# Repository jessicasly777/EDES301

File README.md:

Main control flow of this project 
Blynk App (Joystick)
        ↓
communication.py
        ↓
main.py (control logic)
        ↓
dc_motor.py
        ↓
DRV8833 → Motors

communication.py: Handles all communication between the PocketBeagle and the Blynk mobile application. It connects to the Blynk cloud and reads joystick input from two virtual pins:

V0 for left/right (X-axis)
V1 for forward/backward (Y-axis)

dc_motor.py: Cntrols the DC motors through the DRV8833 motor driver. Each motor is controlled using two pins:

A PWM pin for speed control
A GPIO pin for direction

The module provides simple methods:

forward(speed)
backward(speed)
stop()
cleanup()

limit_switch.py: This module implements an emergency stop mechanism using a physical limit switch.

pin.sh: Cnfigures the PocketBeagle pins before running the system.

main.py: Initializes all components, including the communication module, motor drivers, and limit switch. It then runs a continuous loop that:

test_motor.py: This file is used to test each motor individually. It runs a sequence where each motor moves forward, stops, moves backward, and stops again. This helps verify that wiring and control logic are correct before running the full system. **If a motor spins in the wrong direction, the wires on the motor driver should be swapped rather than modifying the code.** 

test_blynk.py: Tests the connection to the Blynk cloud. It confirms that the PocketBeagle can establish a connection and communicate with the app. This is useful for debugging network issues independently from the rest of the system.

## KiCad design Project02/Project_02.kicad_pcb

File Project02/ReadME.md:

# EDES 301 Project 02 — PocketBeagle TFT PCB

## Project Overview

This project is a two-sided PCB design for a PocketBeagle-based interface board. The board includes an Adafruit 2.8" TFT display, two push buttons, two potentiometers, three LEDs with current-limiting resistors, and a USB connector.

The PCB was designed in KiCad and prepared for manufacturing quote review through MacroFab.

## Board Description

The board is designed as a 5 in × 4 in two-sided PCB.

### Front Side Components

The front side contains the user-interface components:

- Adafruit 2.8" TFT display
- Two push buttons
- Two potentiometers
- Three LEDs
- LED current-limiting resistors

### Back Side Components

The back side contains the main controller and USB connector:

- PocketBeagle
- USB Type-A connector

## Major Electrical Connections

### TFT Display

The Adafruit TFT footprint includes many additional pads for features such as SD card, touchscreen, and interface configuration. This project only uses the SPI display interface.

The routed TFT pins are:

- `GND` → Ground
- `3-5V` → +5 V
- `CLK` → PocketBeagle SPI clock
- `MOSI` → PocketBeagle SPI MOSI
- `MISO` → PocketBeagle SPI MISO
- `CS` → TFT chip select GPIO
- `D/C` → TFT data/command GPIO
- `RST` → TFT reset GPIO

Unused TFT-related pads may include:

- `Card Detect`
- `Card CS`
- `M0`
- `M1`
- `M2`
- `M3`
- `X+`
- `X-`
- `Y+`
- `Y-`
- `3.3V out`
- other unused breakout-board pads

These pads are intentionally left unconnected because the project does not use SD card, touchscreen, or alternate interface features.

### Potentiometers

Each potentiometer is connected as a voltage divider:

- One side to `GND`
- One side to `+1V8`
- Wiper to a PocketBeagle analog input

### Push Buttons

Each push button is connected between a PocketBeagle GPIO input and ground.

### LEDs

Each LED is connected through a current-limiting resistor to a PocketBeagle GPIO pin and ground.

### USB Connector

The USB connector is used for power and/or board access depending on the final configuration.

Basic connections include:

- `VBUS` → +5 V
- `GND` → Ground
- Shield → Ground, if connected in final layout

## PCB Design Rules

The design follows the class PCB design-rule target where possible:

- Signal trace width: 10 mil typical
- Signal clearance: 5–10 mil
- Power trace width: approximately 15 mil where space allows
- Via size: 24 mil
- Via drill: 12 mil

In dense areas near the TFT and PocketBeagle headers, 5 mil routing/clearance may be used where necessary to complete routing.

## Known Warnings / Final PCB Notes

The final PCB design may contain warnings related to unused pads on the Adafruit TFT footprint.

These warnings are expected because the Adafruit TFT breakout footprint includes additional physical pads for optional features that are not used in this design, including SD card, touchscreen, and configuration pins.

The required TFT display pins are routed. The unused TFT pads are intentionally left unconnected.

Warnings that were reviewed and considered acceptable:

- Unused TFT breakout-board pads with no assigned schematic connection
- Optional TFT feature pins not used in this project
- Silkscreen or labeling warnings that do not affect electrical operation, if present

Errors that should not be ignored:

- Copper clearance violations
- Short circuits
- Unconnected required nets
- Missing board outline
- Incorrect footprint-to-symbol pin matching for required signals

## Library Components Created or Imported

Custom or imported library components used in this project include:

- PocketBeagle symbol/footprint
- Adafruit 2.8" TFT breakout footprint
- Custom simplified Adafruit TFT schematic symbol
- Potentiometer symbol/footprint, if modified or imported
- USB_A symbol/footprint, if imported

Standard KiCad components such as resistors, LEDs, and push buttons were used where appropriate.

## Manufacturing Files

The generated manufacturing package includes:

- Gerber files
- Drill files
- PCB layout files
- Schematic PDF
- Bill of Materials
- PCB screenshots
- MacroFab quote documentation

Gerber layers include:

- Front copper
- Back copper
- Front solder mask
- Back solder mask
- Front silkscreen
- Back silkscreen
- Edge cuts
- Drill files

## MacroFab Quote

A MacroFab quote was generated for the completed PCB design. The quote shows a volume discount, where the per-unit cost decreases as the order quantity increases.

Quoted quantities include low-volume prototype and larger production quantities.

## Documentation Screenshots

The project documentation includes screenshots of:

- Full schematic
- Front PCB layout
- Back PCB layout
- 3D PCB view, if available
- Design Rule Check result
- MacroFab price break / quote page

## Final Notes

## Final Notes

The final PCB still has a few KiCad warnings. The remaining warnings are mostly from small leftover routing features and silkscreen details.

One warning is for an unconnected track end on `Net-(U1-GPIO27)`. Another warning is for a via on `Net-(U1-GPIO20)` that is not fully connected on both layers. These are likely from leftover or partial routing segments during layout cleanup. If this board were revised again, I would remove or reconnect those small segments.

There are also silkscreen clipping warnings from the TFT footprint near the board edge. These warnings affect the printed outline/text only and should not change the electrical function of the board.

The Adafruit TFT footprint also includes extra pads for features such as the SD card, touchscreen, and configuration pins. This Etch-a-Sketch design only uses the display SPI pins, so the unused TFT pads are intentionally left unconnected.

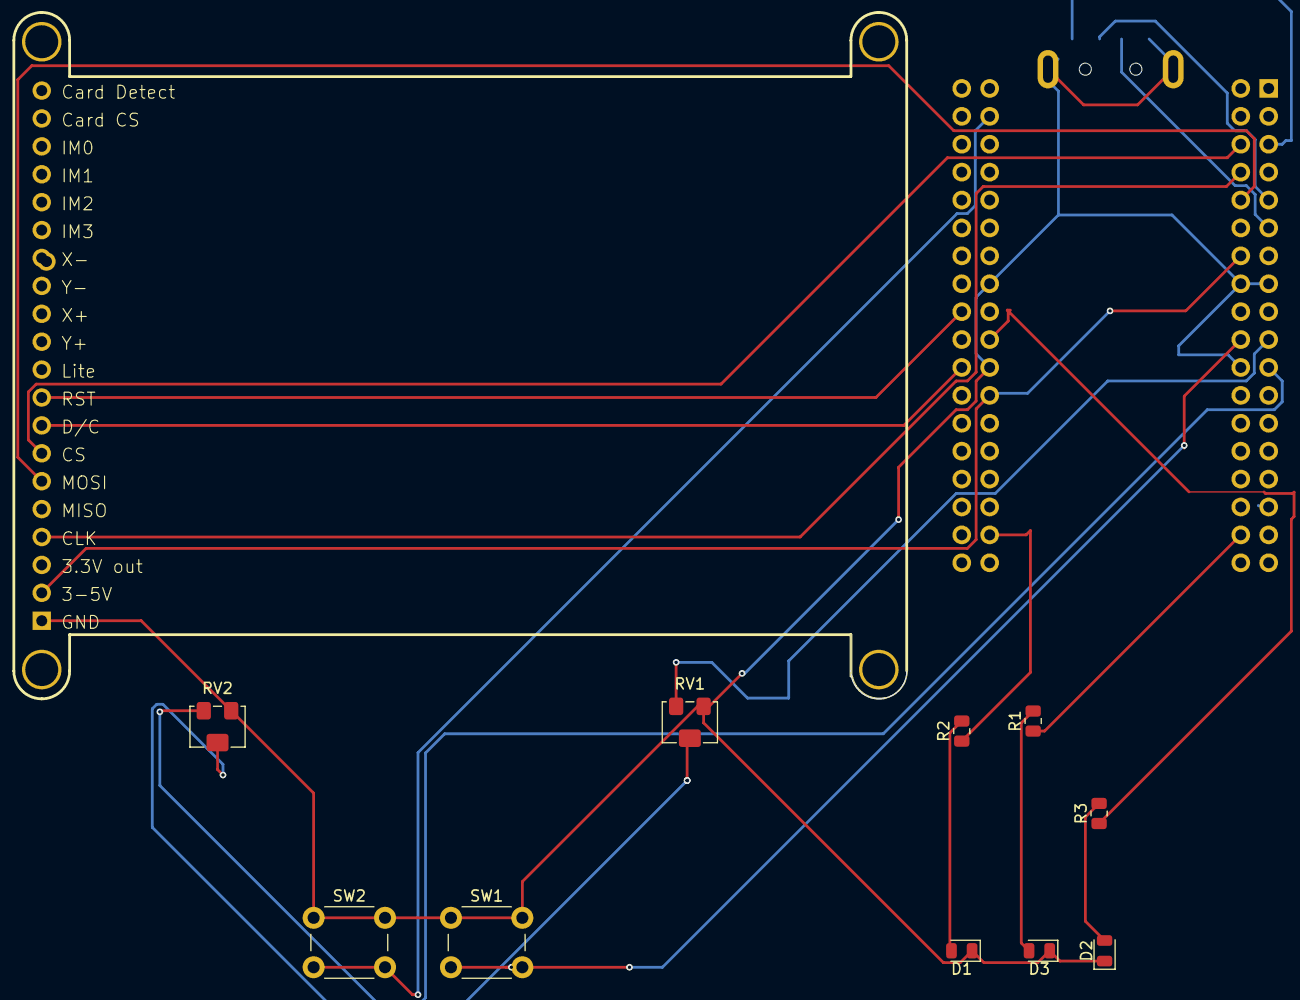
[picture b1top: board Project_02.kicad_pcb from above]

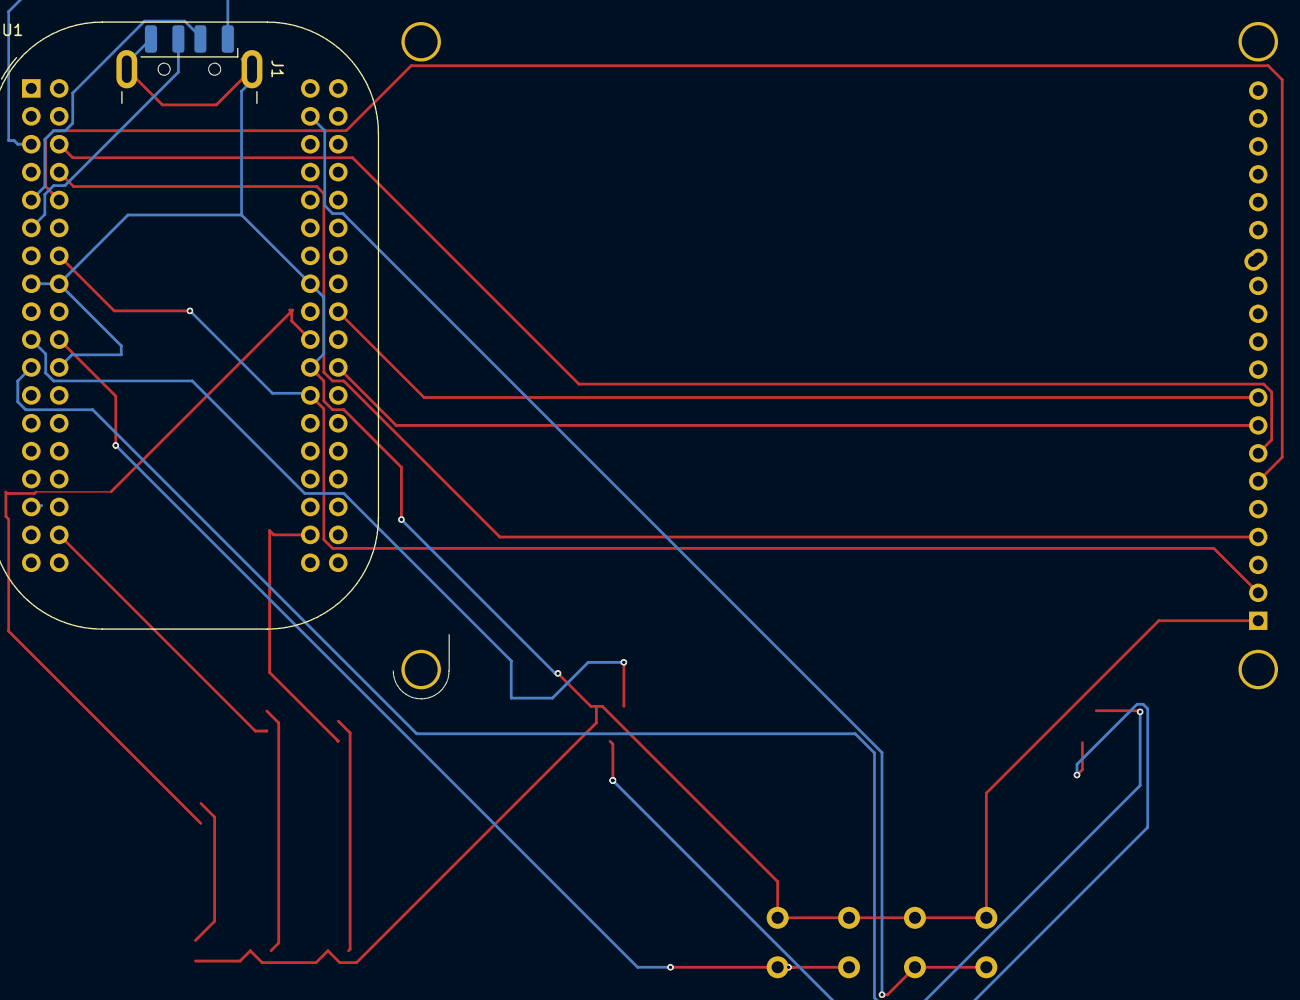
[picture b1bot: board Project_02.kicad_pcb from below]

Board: 4 copper layers, 13 parts (2 on the bottom side), 21 nets.

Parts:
D1, D2, D3: LED; LED_0805_2012Metric
D8: Adafruit tft
J1: USB_A; USB_A_CNCTech_1001-011-01101_Horizontal
R1, R2, R3: R; R_0805_2012Metric
RV1, RV2: R_Potentiometer; Potentiometer_Bourns_3224W_Vertical
SW1, SW2: SW_Push; SW_PUSH_6mm
U1: PocketBeagle; BeagleBoard_PocketBeagle

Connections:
+1V8: RV1.2, RV2.2
+3V3: D8.2 (3-5V), U1.14 (3.3V), U1.59 (3.3V)
+5V: J1.1 (VBUS), U1.5 (USB1.VBUS)
/SPIO_MOSI: D8.6 (MOSI), U1.10 (SPI0.MISO)
/SPIO_SCLK: D8.4 (CLK), U1.8 (SPI0.CLK)
/TFT_CS: D8.7 (CS), U1.6 (SPI0.CS)
/TFT_DC: D8.8 (D/C), U1.58 (GPIO46)
/TFT_RST: D8.9 (RST), U1.54 (GPIO47)
GND: D1.1 (K), D2.1 (K), D3.1 (K), D8.1 (GND), J1.4 (GND), J1.SH (Shield), RV1.1, RV2.1, SW1.1, SW2.1, U1.15 (GND), U1.16 (GND), U1.22 (GND), U1.51 (GND), U1.57 (GND)
unnamed: D1.2 (A), R2.2
unnamed: D2.2 (A), R3.2
unnamed: D3.2 (A), R1.2
unnamed: J1.3 (D+), U1.11 (USB1.D+)
unnamed: J1.2 (D-), U1.9 (USB1.D-)
unnamed: RV1.3, U1.19 (AIN0(1.8V))
unnamed: RV2.3, U1.21 (AIN1(1.8V))
unnamed: SW1.2, U1.20 (GPIO20)
unnamed: SW2.2, U1.39 (GPIO23)
unnamed: R1.1, U1.34 (GPIO26)
unnamed: R3.1, U1.55 (GPIO27)
unnamed: R2.1, U1.69 (GPIO45)

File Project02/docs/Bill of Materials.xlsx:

Designator | Value | Footprint | Populate
D1 | LED | LED_0805_2012Metric | 1
D2 | LED | LED_0805_2012Metric | 1
D3 | LED | LED_0805_2012Metric | 1
D8 | ~ | Adafruit tft | 1
J1 | USB_A | USB_A_CNCTech_1001-011-01101_Horizontal | 1
R1 | R | R_0805_2012Metric | 1
R2 | R | R_0805_2012Metric | 1
R3 | R | R_0805_2012Metric | 1
RV1 | R_Potentiometer | Potentiometer_Bourns_3224W_Vertical | 1
RV2 | R_Potentiometer | Potentiometer_Bourns_3224W_Vertical | 1
SW1 | SW_Push | SW_PUSH_6mm | 1
SW2 | SW_Push | SW_PUSH_6mm | 1
U1 | PocketBeagle | BeagleBoard_PocketBeagle | 1

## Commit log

2026-05-04 Rename communication.py to Project01/communication.py
2026-05-04 Rename config_pin.sh to Project01/config_pin.sh
2026-05-04 Rename dc_motor.py to Project01/dc_motor.py
2026-05-04 Rename limit_switch.py to Project01/limit_switch.py
2026-05-04 Rename main.py to Project01/main.py
2026-05-04 Rename rc_car.py to Project01/rc_car.py
2026-05-04 Rename test_blynk.py to Project01/test_blynk.py
2026-05-04 Rename test_motor.py to Project01/test_motor.py
2026-05-04 Rename test_switch.py to Project01/test_switch.py
2026-05-04 Create Project02
2026-05-04 Add files via upload
    Version 1 Mech Diagram Design
2026-05-04 Rename Project02/EDES301_project_02.pptx to Project02/docs/EDES301_project_02.pptx
2026-05-06 Add files via upload
    Updated Shcematics
2026-05-06 Rename project_02_schematics_pdf.pdf to project_02_final_schematics.pdf
2026-05-06 Rename Project02/Project_02-B_Cu.gbr to Project02/MFG/Project_02-B_Cu.gbr
